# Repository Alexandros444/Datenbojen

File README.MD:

# Datenbojen
In diesem Projekt wird die Umsetzung einer autonomen Datenerfassungsplattform dokumentiert.

## Bachelorarbeit
Genaueres zu dem Projekt kann in der Bachelorarbeit von Alexander Mohr nachgelesen werden.
[Bachelorarbeit](docs/Datenbojen_Bachelor_Arbeit.pdf)

## Ausstellung
Ein Prototyp des Projekts wurde im Berliner Humboldt Forum ausgestellt.

## Rückfragen
- Email an a.mohr@campus.tu-berlin.de

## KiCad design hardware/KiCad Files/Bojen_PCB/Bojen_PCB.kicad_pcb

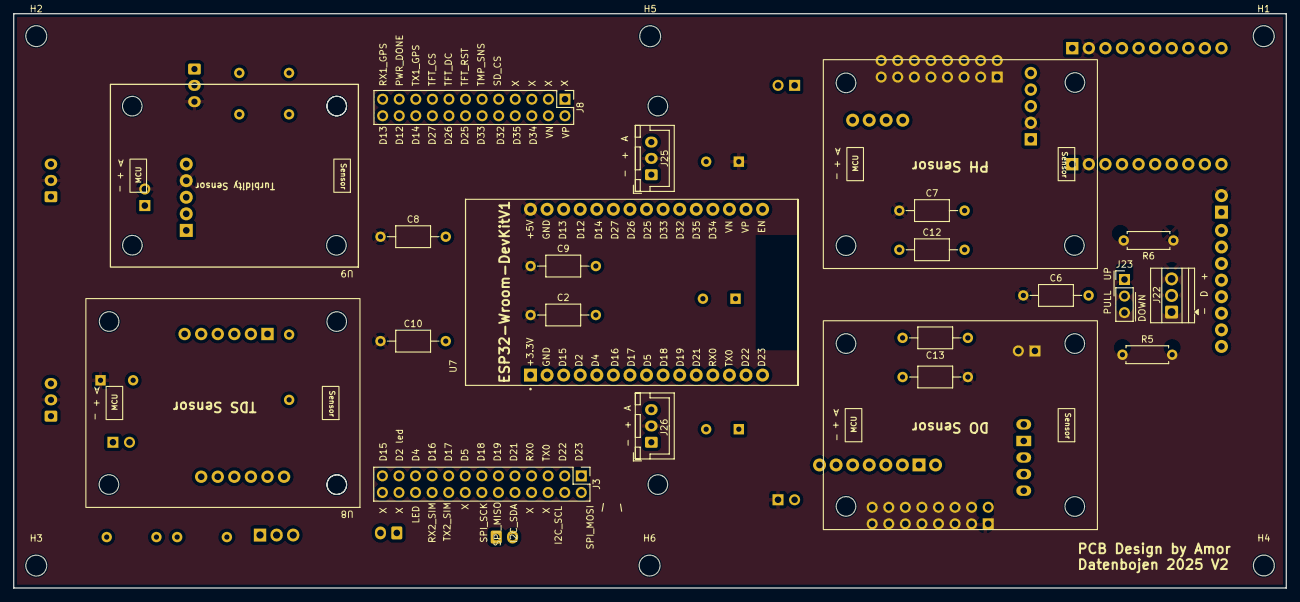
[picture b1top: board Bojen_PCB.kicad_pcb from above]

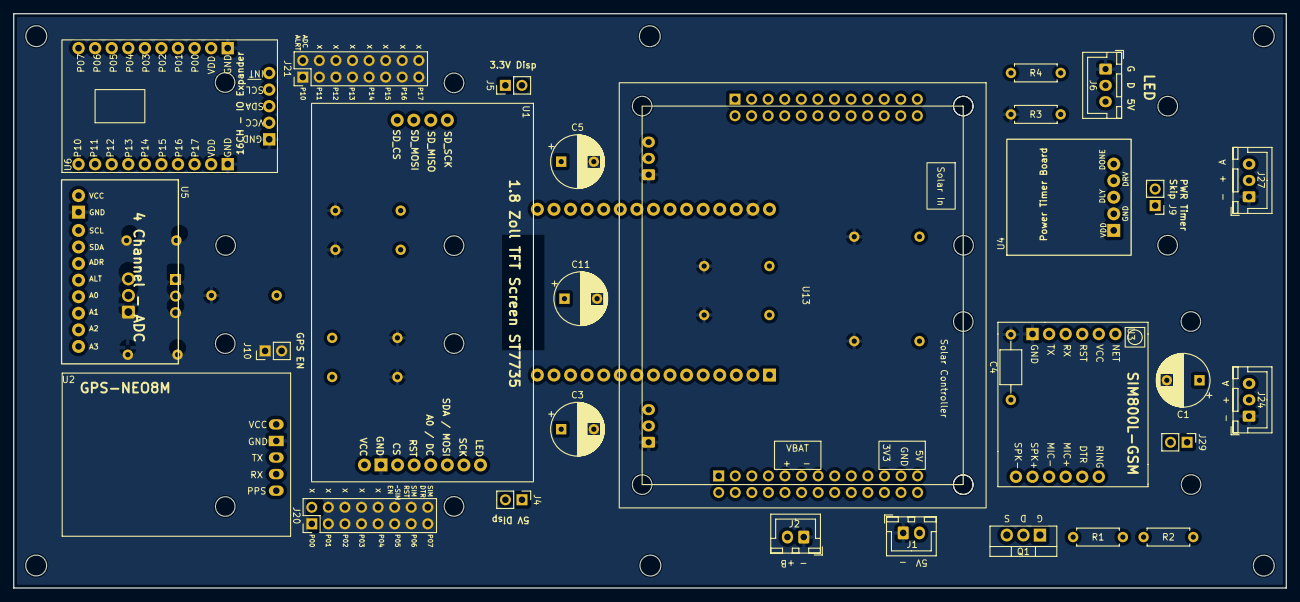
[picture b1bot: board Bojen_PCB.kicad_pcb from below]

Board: 2 copper layers, 195.0 x 88.0 mm, 57 parts (29 on the bottom side), 79 nets, no tracks yet.

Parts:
C1, C3, C5, C11: 100u; CP_Radial_D8.0mm_P5.00mm
C2, C4, C6, C6#2, C12: 10u; C_Axial_L5.1mm_D3.1mm_P10.00mm_Horizontal
C7, C9, C13: 1u; C_Axial_L5.1mm_D3.1mm_P10.00mm_Horizontal
C8, C10: ?; C_Axial_L5.1mm_D3.1mm_P10.00mm_Horizontal
H1, H2, H3, H4, H5, H6: MountingHole; MountingHole_3.2mm_M3
J1: 5V Power In; JST_XH_B2B-XH-A_1x02_P2.50mm_Vertical
J2: Battery Voltage; JST_XH_B2B-XH-A_1x02_P2.50mm_Vertical
J3: GPIO Breakout 2; PinHeader_2x13_P2.54mm_Vertical
J4: 5V TFT; PinHeader_1x02_P2.54mm_Vertical
J5: 3.3V TFT; PinHeader_1x02_P2.54mm_Vertical
J6: LED; JST_XH_B3B-XH-A_1x03_P2.50mm_Vertical
J8: GPIO Breakout 1; PinHeader_2x12_P2.54mm_Vertical
J9: PWR TMR SKIP; PinHeader_1x02_P2.54mm_Vertical
J10: GPS EN; PinHeader_1x02_P2.54mm_Vertical
J20: PCF_GPIO1; PinHeader_2x08_P2.54mm_Vertical
J21: PCF_GPIO2; PinHeader_2x08_P2.54mm_Vertical
J22: TMP Sens; TerminalBlock_Xinya_XY308-2.54-3P_1x03_P2.54mm_Horizontal
J23: TMP PULL UP / DOWN; PinHeader_1x03_P2.54mm_Vertical
J24: TDS Sens; JST_XH_B3B-XH-A_1x03_P2.50mm_Vertical
J25: PH Sens; JST_XH_B3B-XH-A_1x03_P2.50mm_Vertical
J26: DO Sens; JST_XH_B3B-XH-A_1x03_P2.50mm_Vertical
J27: TRB Sens; JST_XH_B3B-XH-A_1x03_P2.50mm_Vertical
J29: Sim PWR Skip; PinHeader_1x02_P2.54mm_Vertical
Q1: IRF5210PBF; TO-220-3_Vertical
R1, R5, R6: 10k; R_Axial_DIN0207_L6.3mm_D2.5mm_P7.62mm_Horizontal
R2: 470; R_Axial_DIN0207_L6.3mm_D2.5mm_P7.62mm_Horizontal
R3: 220k; R_Axial_DIN0207_L6.3mm_D2.5mm_P7.62mm_Horizontal
R4: 330; R_Axial_DIN0207_L6.3mm_D2.5mm_P7.62mm_Horizontal
U1: Display_TFT_1.8Zoll_ST7735; ST7735 TFT Screen 1.8 Zoll no hole
U2: NEO-GPS8M; GY-NEO8MV2 no hole
U3: SIM800L-CORE
U4: TLP5110 Power Timer Modul; TPL5110 Board no hole
U5: ADC - ADS1115 Module; ADC - ADS1115 Module no hole
U6: PCF8575 Module; 16-bit IO Expander
U7: ESP32-DEVKIT-V1; MODULE_ESP32_DEVKIT_V1 no hole
U8: TDS Sensor; TDS Sensor DFRobot
U9: Turbidity Sensor; Turbidity Sensor DFRobot
U11: DO Sensor; DO Sensor DFRobot
U13: Solar Controller; Solar Power MPPT Module
U15: PH Sensor; PH Sensor DFRobot

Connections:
+3.3V: C11.1, C12.1, C13.1, J5.2, U7.1 (3V3)
+5V: C1.1, C2.1, C5.1, C6.1, C6#2.1, C7.1, C8.1, C9.1, C10.1, J4.1, J6.3, J9.2, J10.2, J22.3, J24.2, J25.2, J26.2, J27.2, R6.1, U4.4 (DRV), U5.1 (VCC), U6.9 (VDD), U6.12 (VDD), U6.C2 (VCC), U7.30 (VIN)
+BATT: J2.2, J29.1, Q1.3 (S), R1.1
/ADC_ALRT: J21.2, U5.6 (ALRT)
/ESP32/D2: J3.23, U7.4 (D2)
/ESP32/D4: J3.21, U7.5 (D4)
/ESP32/D5: J3.15, U7.8 (D5)
/ESP32/D12: J8.22, U7.27 (D12)
/ESP32/D13: J8.24, U7.28 (D13)
/ESP32/D14: J8.20, U7.26 (D14)
/ESP32/D15: J3.25, U7.3 (D15)
/ESP32/D18: J3.13, U7.9 (D18)
/ESP32/D19: J3.11, U7.10 (D19)
/ESP32/D21: J3.9, U7.11 (D21)
/ESP32/D22: J3.3, U7.14 (D22)
/ESP32/D23: J3.1, U7.15 (D23)
/ESP32/D25: J8.14, U7.23 (D25)
/ESP32/D26: J8.16, U7.24 (D26)
/ESP32/D27: J8.18, U7.25 (D27)
/ESP32/D32: J8.10, U7.21 (D32)
/ESP32/D33: J8.12, U7.22 (D33)
/ESP32/D34: J8.6, U7.19 (D34)
/ESP32/D35: J8.8, U7.20 (D35)
/ESP32/RX0: J3.7, U7.12 (RX0)
/ESP32/RX2: J3.19, U7.6 (RX2)
/ESP32/TX0: J3.5, U7.13 (TX0)
/ESP32/TX2: J3.17, U7.7 (TX2)
/ESP32/VN: J8.4, U7.18 (VN)
/ESP32/VP: J8.2, U7.17 (VP)
/I2C_SCL: J3.4, U5.3 (SCL), U6.C4 (SCL)
/I2C_SDA: J3.10, U5.4 (SDA), U6.C3 (SDA)
/LED_D: J3.22, R4.2
/P00: J20.1, U6.13 (P00)
/P01: J20.3, U6.14 (P01)
/P02: J20.5, U6.15 (P02)
/P03: J20.7, U6.16 (P03)
/P04: J20.9, U6.17 (P04)
/P05: J20.11, U6.18 (P05)
/P06: J20.13, U6.19 (P06)
/P07: J20.15, U6.20 (P07)
/P10: J21.1, U6.1 (P10)
/P11: J21.3, U6.2 (P11)
/P12: J21.5, U6.3 (P12)
/P13: J21.7, U6.4 (P13)
/P14: J21.9, U6.5 (P14)
/P15: J21.11, U6.6 (P15)
/P16: J21.13, U6.7 (P16)
/P17: J21.15, U6.8 (P17)
/PWR_Done: J8.21, U4.5 (Done)
/RX1: J8.23, U2.3 (TX)
/RX2: J3.20, U3.5 (TXD)
/SD_CS: J8.9, U1.9 (SD_CS)
/SIM_DTR: J20.16, U3.11 (DTR)
/SIM_RST: J20.14, U3.3 (RST)
/SPI_MISO: J3.12, U1.11 (SD_MISO)
/SPI_MOSI: J3.2, U1.3 (TFT_SDA_MOSI), U1.10 (SD_MOSI)
/SPI_SCK: J3.14, U1.2 (TFT_SCK), U1.12 (SD_SCK)
/TFT_CS: J8.17, U1.6 (TFT_CS)
/TFT_DC: J8.15, U1.4 (TFT_A0_DC)
/TFT_RST: J8.13, U1.5 (TFT_RST)
/TMP_SENS: J8.11, J22.2, J23.2
/TX1: J8.19, U2.4 (RX)
/TX2: J3.18, U3.4 (RXD)
/sensors/ADC0: J24.3, U5.7 (A0)
/sensors/ADC1: J25.3, U5.8 (A1)
/sensors/ADC2: J26.3, U5.9 (A2)
/sensors/ADC3: J27.3, U5.10 (A3)
/~SIM_EN: J20.12, R2.1
GND: C1.2, C2.2, C3.2, C4.2, C5.2, C6.2, C6#2.2, C7.2, C8.2, C9.2, C10.2, C11.2, C12.2, C13.2, J1.1, J2.1, J6.1, J22.1, J24.1, J25.1, J26.1, J27.1, R3.2, R5.2, U1.7 (GND), U2.2 (GND), U3.6 (GND), U4.2 (GND), U5.2 (GND), U6.10 (GND), U6.11 (GND), U6.C1 (GND), U7.2 (GND), U7.29 (GND)
unnamed: J1.2, J9.1, U4.1 (VDD)
unnamed: J4.2, U1.8 (VCC)
unnamed: J5.1, U1.1 (TFT_LED)
unnamed: J6.2, R4.1
unnamed: J10.1, U2.1 (VCC)
unnamed: J23.1, R6.2
unnamed: J23.3, R5.1
unnamed: C3.1, C4.1, J29.2, Q1.2 (D), U3.2 (VCC)
unnamed: Q1.1 (G), R1.2, R2.2
unnamed: R3.1, U4.3 (Delay)

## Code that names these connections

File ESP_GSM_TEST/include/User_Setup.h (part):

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// The DC (Data Command) pin may be labelled AO or RS (Register Select)
//
// With some displays such as the ILI9341 the TFT CS pin can be connected to GND if no more
// SPI devices (e.g. an SD Card) are connected, in this case comment out the #define TFT_CS
// line below so it is NOT defined. Other displays such at the ST7735 require the TFT CS pin
// to be toggled during setup, so in these cases the TFT_CS line must be defined and connected.
//
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#define TFT_MOSI  23  // aka. SDA Automatically assigned with ESP8266 if not defined
#define TFT_SCLK  18  // Automatically assigned with ESP8266 if not defined

#define TFT_CS    27  // Chip select control pin D8
#define TFT_DC    26  // aka. A0 Data Command control pin
#define TFT_RST   25  // Reset pin (could connect to NodeMCU RST, see next line)
//#define TFT_RST  -1     // Set TFT_RST to -1 if the display RESET is connected to NodeMCU RST or 3.3V


// #define TFT_BL 25  // LED back-light (only for ST7789 with backlight control pin)
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//#define TFT_SPI_OVERLAP

// In ESP8266 overlap mode the TFT chip select MUST connect to pin D3
//#define TFT_CS   PIN_D3
//#define TFT_DC   PIN_D5  // Data Command control pin
//#define TFT_RST  PIN_D4  // Reset pin (could connect to NodeMCU RST, see next line)
//#define TFT_RST  -1  // Set TFT_RST to -1 if the display RESET is connected to NodeMCU RST or 3.3V


// ###### EDIT THE PIN NUMBERS IN THE LINES FOLLOWING TO SUIT YOUR ESP32 SETUP   ######
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//#define TFT_MISO 19
//#define TFT_MOSI 23
//#define TFT_SCLK 18
//#define TFT_CS   15  // Chip select control pin
//#define TFT_DC    2  // Data Command control pin
//#define TFT_RST   4  // Reset pin (could connect to RST pin)
//#define TFT_RST  -1  // Set TFT_RST to -1 if display RESET is connected to ESP32 board RST

// For ESP32 Dev board (only tested with GC9A01 display)
// The hardware SPI can be mapped to any pins

//#define TFT_MOSI 15 // In some display driver board, it might be written as "SDA" and so on.
//#define TFT_SCLK 14
//#define TFT_CS   5  // Chip select control pin
//#define TFT_DC   27  // Data Command control pin
//#define TFT_RST  33  // Reset pin (could connect to Arduino RESET pin)
//#define TFT_BL   22  // LED back-light

//#define TOUCH_CS 21     // Chip select pin (T_CS) of touch screen
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//#define TFT_MISO 19
//#define TFT_MOSI 23
//#define TFT_SCLK 18
//#define TFT_CS   14  // Chip select control pin
//#define TFT_DC   27  // Data Command control pin
//#define TFT_RST  33  // Reset pin (could connect to Arduino RESET pin)
//#define TFT_BL   32  // LED back-light (required for M5Stack)

// ######       EDIT THE PINs BELOW TO SUIT YOUR ESP32 PARALLEL TFT SETUP        ######
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//#define TFT_PARALLEL_8_BIT

// The ESP32 and TFT the pins used for testing are:
//#define TFT_CS   33  // Chip select control pin (library pulls permanently low
//#define TFT_DC   15  // Data Command control pin - must use a pin in the range 0-31
//#define TFT_RST  32  // Reset pin, toggles on startup

//#define TFT_WR    4  // Write strobe control pin - must use a pin in the range 0-31
//#define TFT_RD    2  // Read strobe control pin
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//#define TFT_SCLK PB13

// Can use Ardiuno pin references, arbitrary allocation, TFT_eSPI controls chip select
//#define TFT_CS   D5 // Chip select control pin to TFT CS
//#define TFT_DC   D6 // Data Command control pin to TFT DC (may be labelled RS = Register Select)
//#define TFT_RST  D7 // Reset pin to TFT RST (or RESET)
// OR alternatively, we can use STM32 port reference names PXnn
//#define TFT_CS   PE11 // Nucleo-F767ZI equivalent of D5
//#define TFT_DC   PE9  // Nucleo-F767ZI equivalent of D6
//#define TFT_RST  PF13 // Nucleo-F767ZI equivalent of D7

//#define TFT_RST  -1   // Set TFT_RST to -1 if the display RESET is connected to processor reset
                        // Use an Arduino pin for initial testing as connecting to processor reset
                        // may not work (pulse too short at power up?)

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
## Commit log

2025-03-15 leds and http self at
2025-03-15 working self coded AT command
2025-03-15 code aufgeräumt, wait for resp todo
2025-03-17 Add new directory
2025-03-17 Raspberry Config
2025-03-17 Add new file
2025-03-18 rc local raspby setup
2025-03-18 backup
2025-03-18 Edit install_documentation.MD
2025-03-19 control.sh
2025-04-09 readme update
2025-04-09 Edit README.MD
2025-04-29 Git Test Kommentar
2025-05-07 rem comment
2025-05-12 Lilly Board Repo geadded
2025-05-12 GSM Test Modul Code
2025-05-18 Webserver Post/Get Upadate
2025-05-19 gps Modul Code
2025-05-19 TFT Screen
2025-05-20 httppara text plain und Readme Lillypad Pinout
2025-05-22 Kicad Initial
2025-05-22 layout
2025-05-23 PCB Design
2025-05-24 PCB V2
2025-05-24 PCB V2 rearange fit tube
2025-05-26 Edit README.MD zrok
2025-06-05 esp auf pcb
2025-06-05 init ESP_LED_TEST
2025-06-05 made every animation somewhat dynamic
2025-06-27 Feedback PCB
2025-06-27 ADS1115 ADC
2025-07-12 PCB Sensor Code complete Refactor, and TFT Screen Sensor Value Display
2025-08-05 tft Screen QR Code Display
2025-08-05 Display Pages
2025-08-06 led module
2025-08-19 Solar Plot Code
2025-08-21 color change works fully, speed needs to be adjusted, mostly ai generated
2025-08-21 forgot to save lol, color change works fully, speed needs to be adjusted, mostly ai generated
2025-08-26 Example function no Delay
2025-08-26 doesnt work but its a start
2025-08-27 Animation fix, wait
2025-08-27 used predefined fill_solid
2025-08-27 Bachelor
2025-08-28 Latex Datenbojen
2025-09-07 Submodule Link to Overleaf Bachelorarbeit
2025-09-07 Submodule Link to Overleaf Bacherlorarbeit
2025-09-10 QR code update, LED integration, Example Visual Data,
2025-09-13 PCB Updated, Fixes
2025-09-16 Exhibition lights for led_module (unfinished)
2025-09-16 gsm info update, display Manager class
2025-09-18 functional exhibitioncolor
2025-09-25 exhibitionlight final touches
2025-09-26 Display Fix, led_module cleanup
2025-09-26 TFT User Setup Fix
2025-09-26 led_module back to one in ten
2025-09-26 longer cycle
2025-09-26 Final Exhibition anim, debug tft print
2025-10-09 PCB Fixes
2025-10-09 LoRa, Timer, GPIO, Wifi
2025-10-09 Lora, Led Test
2025-10-14 idk was hab ich geändert
2025-10-16 System Schematics
2025-10-20 Python Server Data Plot
2025-10-20 python server Rename, pcb Feedback
2025-10-20 testCode, images, SystemTestPlot
2025-10-21 state_module, Bilder
2025-11-17 Bachelor Work
2026-03-04 Restructure
